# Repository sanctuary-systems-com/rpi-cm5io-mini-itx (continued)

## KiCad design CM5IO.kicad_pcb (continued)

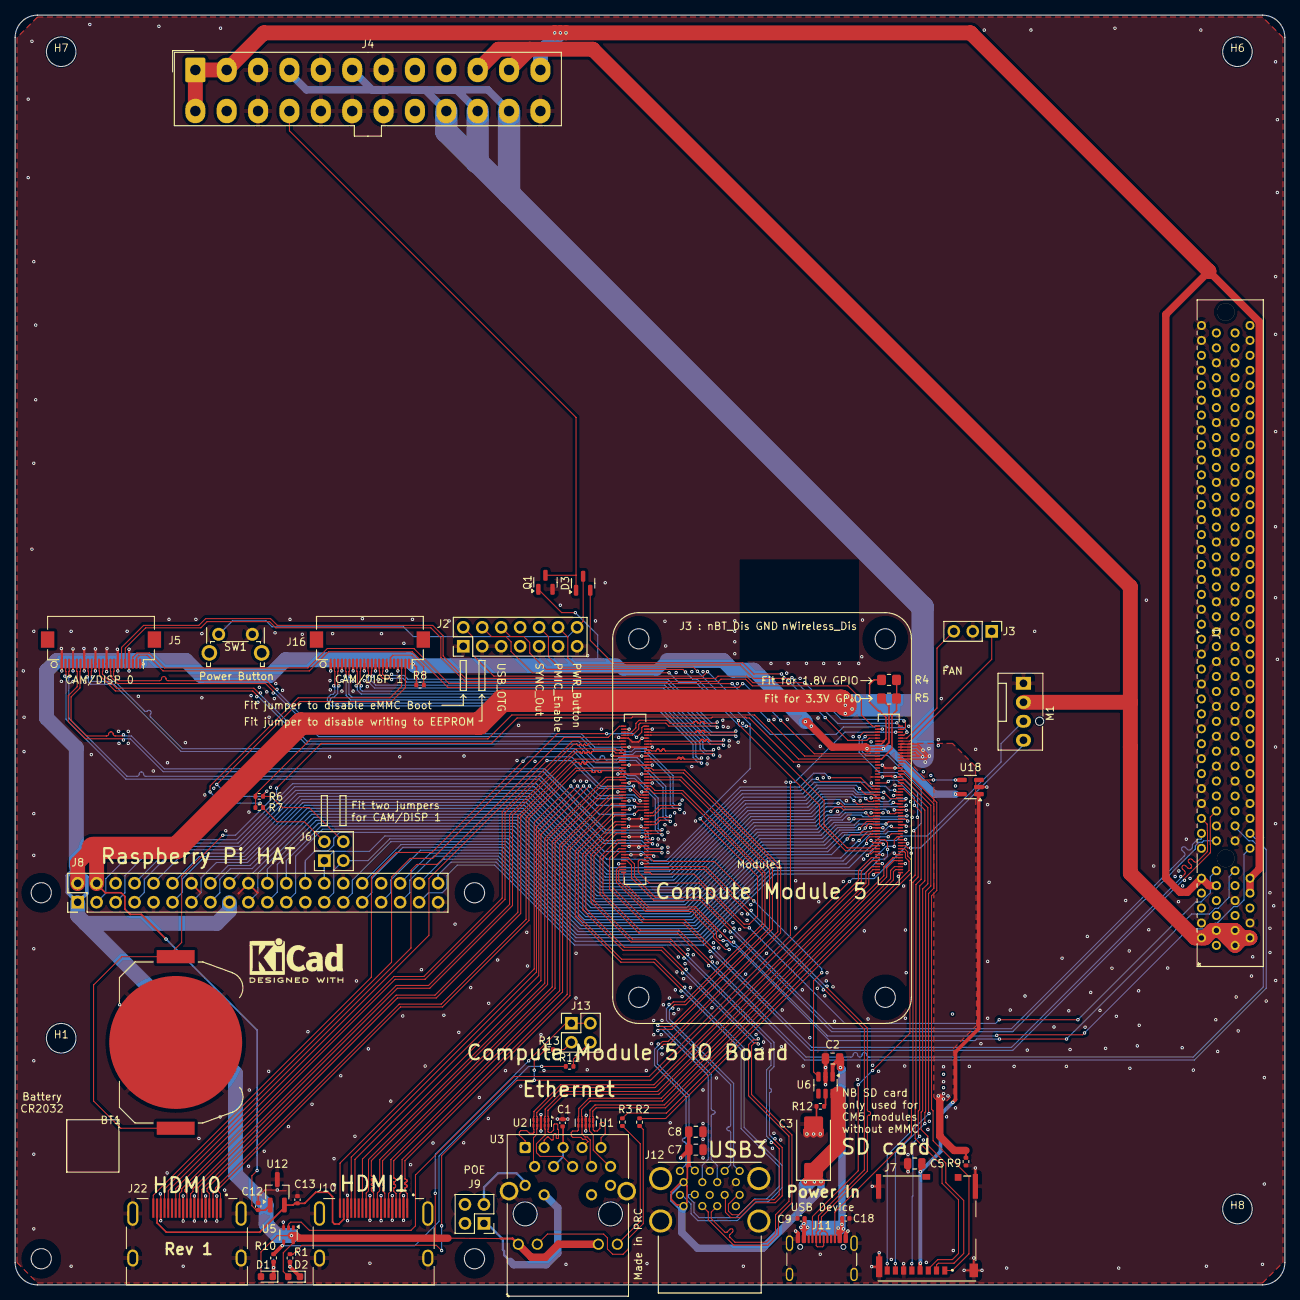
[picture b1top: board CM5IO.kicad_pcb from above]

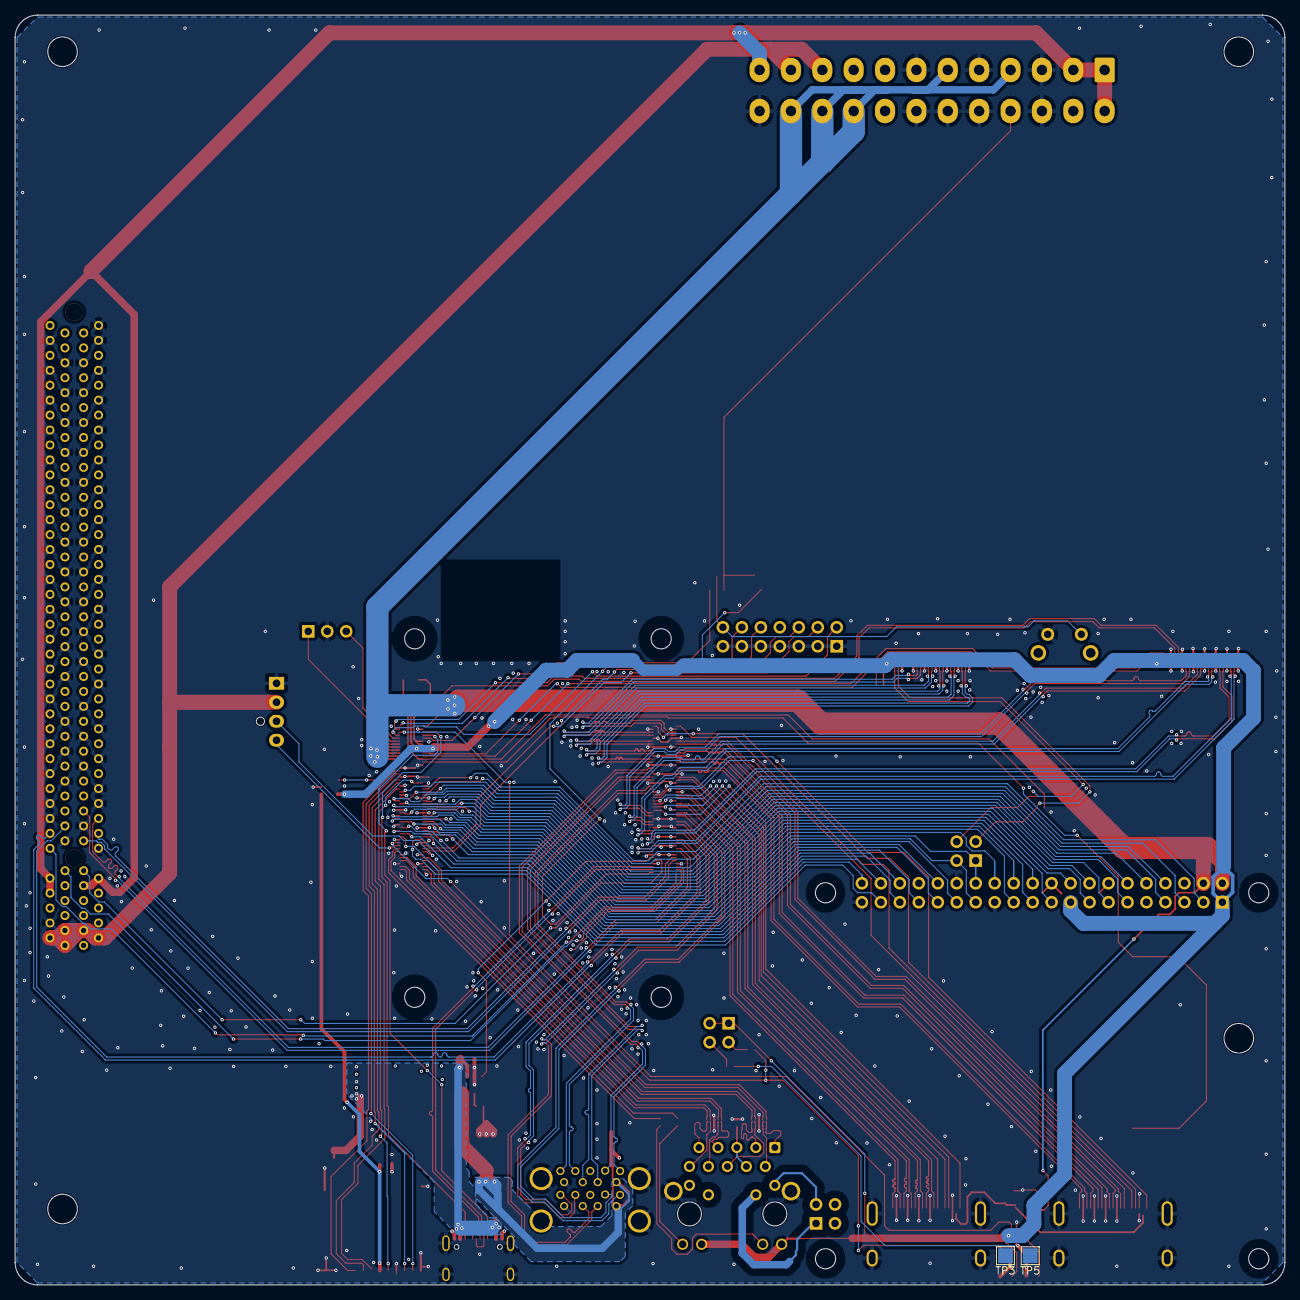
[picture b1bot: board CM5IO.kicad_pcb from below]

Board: 4 copper layers, 170.0 x 170.0 mm, 64 parts (2 on the bottom side), 160 nets.

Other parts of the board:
logo1: KiCad-Logo2_5mm_SilkScreen

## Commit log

2024-11-29 add original rasp io board files
2024-11-29 add modifications so far
2024-12-02 complete first pass at schematic
2024-12-04 first pass at layout
2024-12-09 fix PCIe position and PS_ON logic
2024-12-16 add LCSC part numbers, redo fan header and ps_on logic
2025-01-28 update PCB
2025-01-28 aestetics
2025-03-31 fix differential pair impedance
2025-04-02 add aisler logo
2025-04-11 update drop in replacements
2025-04-11 update ethernet connector
2025-04-11 add fan protection
2025-04-14 add ideal diode to ATX
2025-04-14 more aisler changes
2025-04-16 add dummy pad and more ideal ideal diode
